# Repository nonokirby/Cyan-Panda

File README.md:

# Cyan Panda Expansion Gateway

The open-source hybrid can bus gateway !

Based heabily on the Racoon '[trash panda](https://github.com/mickabrig7/raccoon)'

more info coming **soon™**

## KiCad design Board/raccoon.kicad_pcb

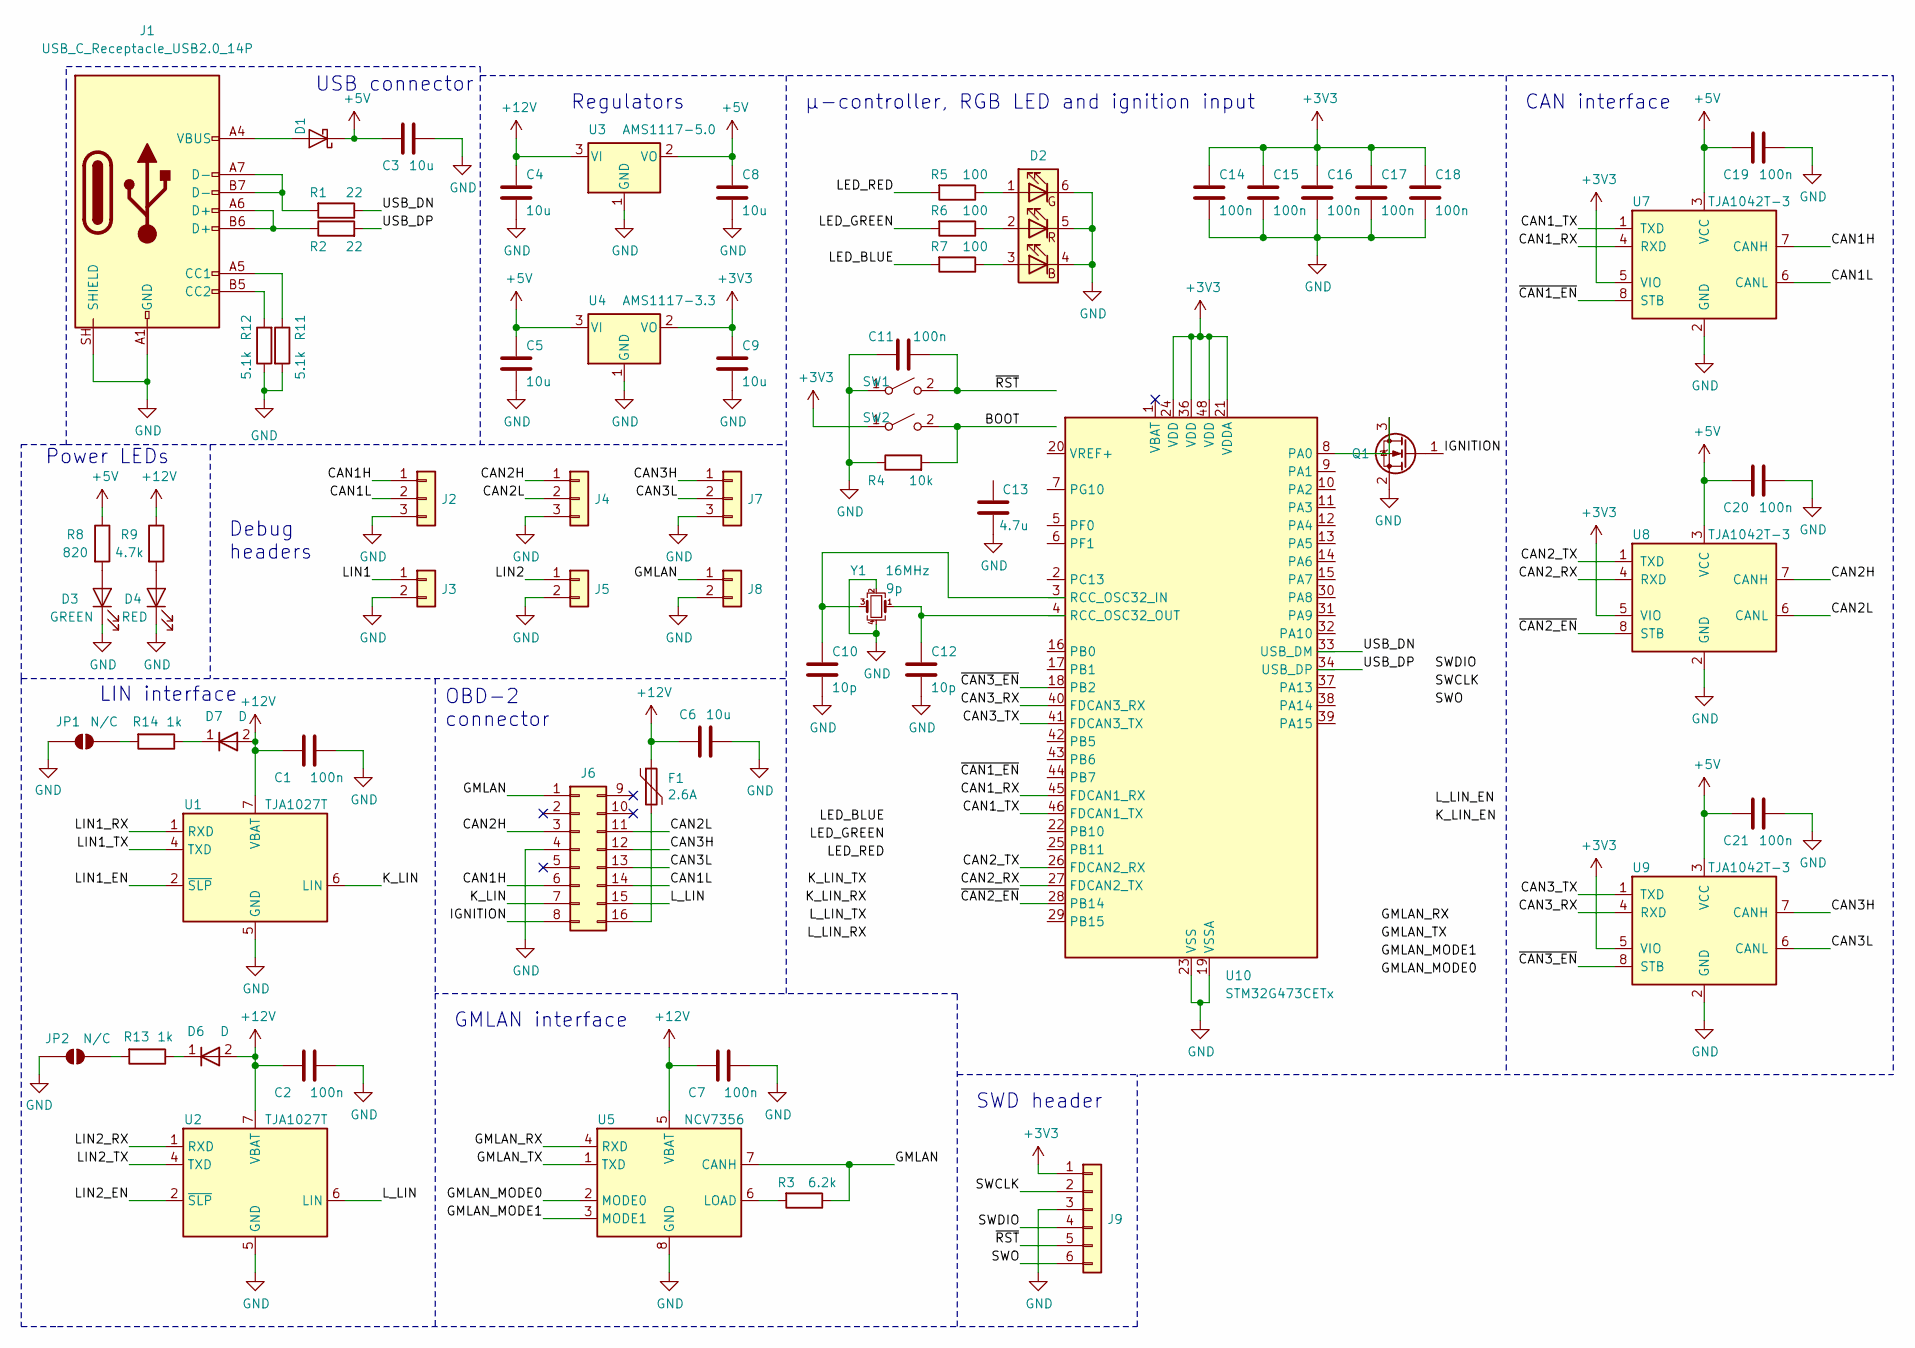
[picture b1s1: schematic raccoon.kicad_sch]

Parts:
C1, C2, C7, C11, C14, C15, C16, C17, C18, C19, C20, C21: 100n; C_0603_1608Metric; LCSC C14663
C3, C4, C5, C6, C8, C9: 10u; C_0805_2012Metric; LCSC C15850
C10, C12: 10p; C_0402_1005Metric; LCSC C32949
C13: 4.7u; C_0603_1608Metric; LCSC C19666
D1: D_Schottky; D_SMA; LCSC C8678
D2: LED_RGB; LED_RGB_5050-6
D3: GREEN; LED_0603_1608Metric_Castellated; LCSC C72043
D4: RED; LED_0603_1608Metric_Castellated; LCSC C2286
D6, D7: D; D_0603_1608Metric
F1: 2.6A; Fuse_1812_4532Metric
J1: USB_C_Receptacle_USB2.0_14P; USB_C_Receptacle_GCT_USB4105-xx-A_16P_TopMnt_Horizontal
J2, J4, J7: Conn_01x03; PinHeader_1x03_P2.54mm_Vertical
J3, J5, J8: Conn_01x02; PinHeader_1x02_P2.54mm_Vertical
J6: Conn_02x08_Top_Bottom; IDC-Header_2x08_P2.54mm_Vertical
J9: Conn_01x06; PinHeader_1x06_P2.54mm_Vertical
JP1, JP2: N/C; SolderJumper-2_P1.3mm_Open_RoundedPad1.0x1.5mm
Q1: Q_NMOS_GSD; SOT-23; LCSC C8545
R1, R2: 22; R_0603_1608Metric; LCSC C23345
R3: 6.2k; R_0603_1608Metric; LCSC C4260
R4: 10k; R_0603_1608Metric; LCSC C25804
R5, R6, R7: 100; R_0603_1608Metric; LCSC C22775
R8: 820; R_0603_1608Metric; LCSC C23253
R9: 4.7k; R_0603_1608Metric; LCSC C23162
R11, R12: 5.1k; R_01005_0402Metric
R13, R14: 1k; R_0402_1005Metric
SW1, SW2: SW_SPST; SW_PUSH_6mm_H8mm
U1, U2: TJA1027T; SOIC-8_3.9x4.9mm_P1.27mm
U3: AMS1117-5.0; SOT-223-3_TabPin2; LCSC C6187
U4: AMS1117-3.3; SOT-223-3_TabPin2; LCSC C6186
U5: NCV7356; SOIC-8_3.9x4.9mm_P1.27mm
U7, U8, U9: TJA1042T-3; SOIC-8_3.9x4.9mm_P1.27mm
U10: STM32G473CETx; LQFP-48_7x7mm_P0.5mm
Y1: 16MHz; Crystal_SMD_3225-4Pin_3.2x2.5mm; LCSC C13738

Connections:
+3V3: C9.1, C14.1, C15.1, C16.1, C17.1, C18.1, J9.1, SW2.1 (A), U4.2 (VO), U7.5 (VIO), U8.5 (VIO), U9.5 (VIO), U10.21 (VDDA), U10.24 (VDD), U10.36 (VDD), U10.48 (VDD)
+5V: C3.2, C5.1, C8.1, C19.2, C20.2, C21.2, D1.1 (K), R8.1, U3.2 (VO), U4.3 (VI), U7.3 (VCC), U8.3 (VCC), U9.3 (VCC)
+12V: C1.2, C2.2, C4.1, C6.2, C7.2, D6.2 (A), D7.2 (A), F1.1, R9.1, U1.7 (VBAT), U2.7 (VBAT), U3.3 (VI), U5.5 (VBAT)
/BOOT: R4.2, SW2.2 (B)
/CAN1H: J2.1, J6.6, U7.7 (CANH)
/CAN1L: J2.2, J6.14, U7.6 (CANL)
/CAN1_RX: U7.4 (RXD), U10.45 (FDCAN1_RX)
/CAN1_TX: U7.1 (TXD), U10.46 (FDCAN1_TX)
/CAN2H: J4.1, J6.3, U8.7 (CANH)
/CAN2L: J4.2, J6.11, U8.6 (CANL)
/CAN2_RX: U8.4 (RXD), U10.27 (FDCAN2_TX)
/CAN2_TX: U8.1 (TXD), U10.26 (FDCAN2_RX)
/CAN3H: J6.12, J7.1, U9.7 (CANH)
/CAN3L: J6.13, J7.2, U9.6 (CANL)
/CAN3_RX: U9.4 (RXD), U10.40 (FDCAN3_RX)
/CAN3_TX: U9.1 (TXD), U10.41 (FDCAN3_TX)
/GMLAN: J6.1, J8.1, R3.1, U5.7 (CANH)
/GMLAN_MODE0: U5.2 (MODE0)
/GMLAN_MODE1: U5.3 (MODE1)
/GMLAN_RX: U5.4 (RXD)
/GMLAN_TX: U5.1 (TXD)
/IGNITION: J6.8, Q1.1 (G)
/K_LIN: J6.7, U1.6 (LIN)
/LED_BLUE: R7.2
/LED_GREEN: R6.2
/LED_RED: R5.2
/LIN1: J3.1
/LIN1_EN: U1.2 (~SLP)
/LIN1_RX: U1.1 (RXD)
/LIN1_TX: U1.4 (TXD)
/LIN2: J5.1
/LIN2_EN: U2.2 (~SLP)
/LIN2_RX: U2.1 (RXD)
/LIN2_TX: U2.4 (TXD)
/L_LIN: J6.15, U2.6 (LIN)
/SWCLK: J9.2
/SWDIO: J9.4
/SWO: J9.6
/USB_DN: R1.1
/USB_DP: R2.2
/~CAN1_EN: U7.8 (STB), U10.16 (PB0)
/~CAN2_EN: U8.8 (STB), U10.28 (PB14)
/~CAN3_EN: U9.8 (STB), U10.18 (PB2)
/~RST: C11.1, J9.5, SW1.2 (B)
GND: C1.1, C2.1, C3.1, C4.2, C5.2, C6.1, C7.1, C8.2, C9.2, C10.2, C11.2, C12.2, C13.1, C14.2, C15.2, C16.2, C17.2, C18.2, C19.1, C20.1, C21.1, D2.4 (BK), D2.5 (GK), D2.6 (RK), D3.1 (K), D4.1 (K), J1.A1 (GND), J1.A12 (GND), J1.B1 (GND), J1.B12 (GND), J1.SH (SHIELD), J2.3, J3.2, J4.3, J5.2, J6.4, J7.3, J8.2, J9.3, JP1.1 (A), JP2.1 (A), Q1.2 (S), R4.1, R11.2, R12.1, SW1.1 (A), U1.5 (GND), U2.5 (GND), U3.1 (GND), U4.1 (GND), U5.8 (GND), U7.2 (GND), U8.2 (GND), U9.2 (GND), U10.19 (VSSA), U10.23 (VSS), U10.35 (VSS), U10.47 (VSS), Y1.2, Y1.4
unnamed: C10.1, Y1.3
unnamed: C12.1, Y1.1
unnamed: D1.2 (A), J1.A4 (VBUS), J1.A9 (VBUS), J1.B4 (VBUS), J1.B9 (VBUS)
unnamed: D2.3 (BA), R7.1
unnamed: D2.2 (GA), R6.1
unnamed: D2.1 (RA), R5.1
unnamed: D3.2 (A), R8.2
unnamed: D4.2 (A), R9.2
unnamed: D6.1 (K), R13.1
unnamed: D7.1 (K), R14.1
unnamed: J1.A5 (CC1), R11.1
unnamed: J1.B5 (CC2), R12.2
unnamed: J1.A6 (D+), J1.B6 (D+), R2.1
unnamed: J1.A7 (D-), J1.B7 (D-), R1.2
unnamed: F1.2, J6.16
unnamed: JP1.2 (B), R14.2
unnamed: JP2.2 (B), R13.2
unnamed: Q1.3 (D), U10.8 (PA0)
unnamed: R3.2, U5.6 (LOAD)

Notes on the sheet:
Power LEDs
GMLAN interface
USB connector
µ-controller, RGB LED and ignition input
LIN interface
OBD-2 connector
SWD header
CAN interface
Debug headers
Regulators

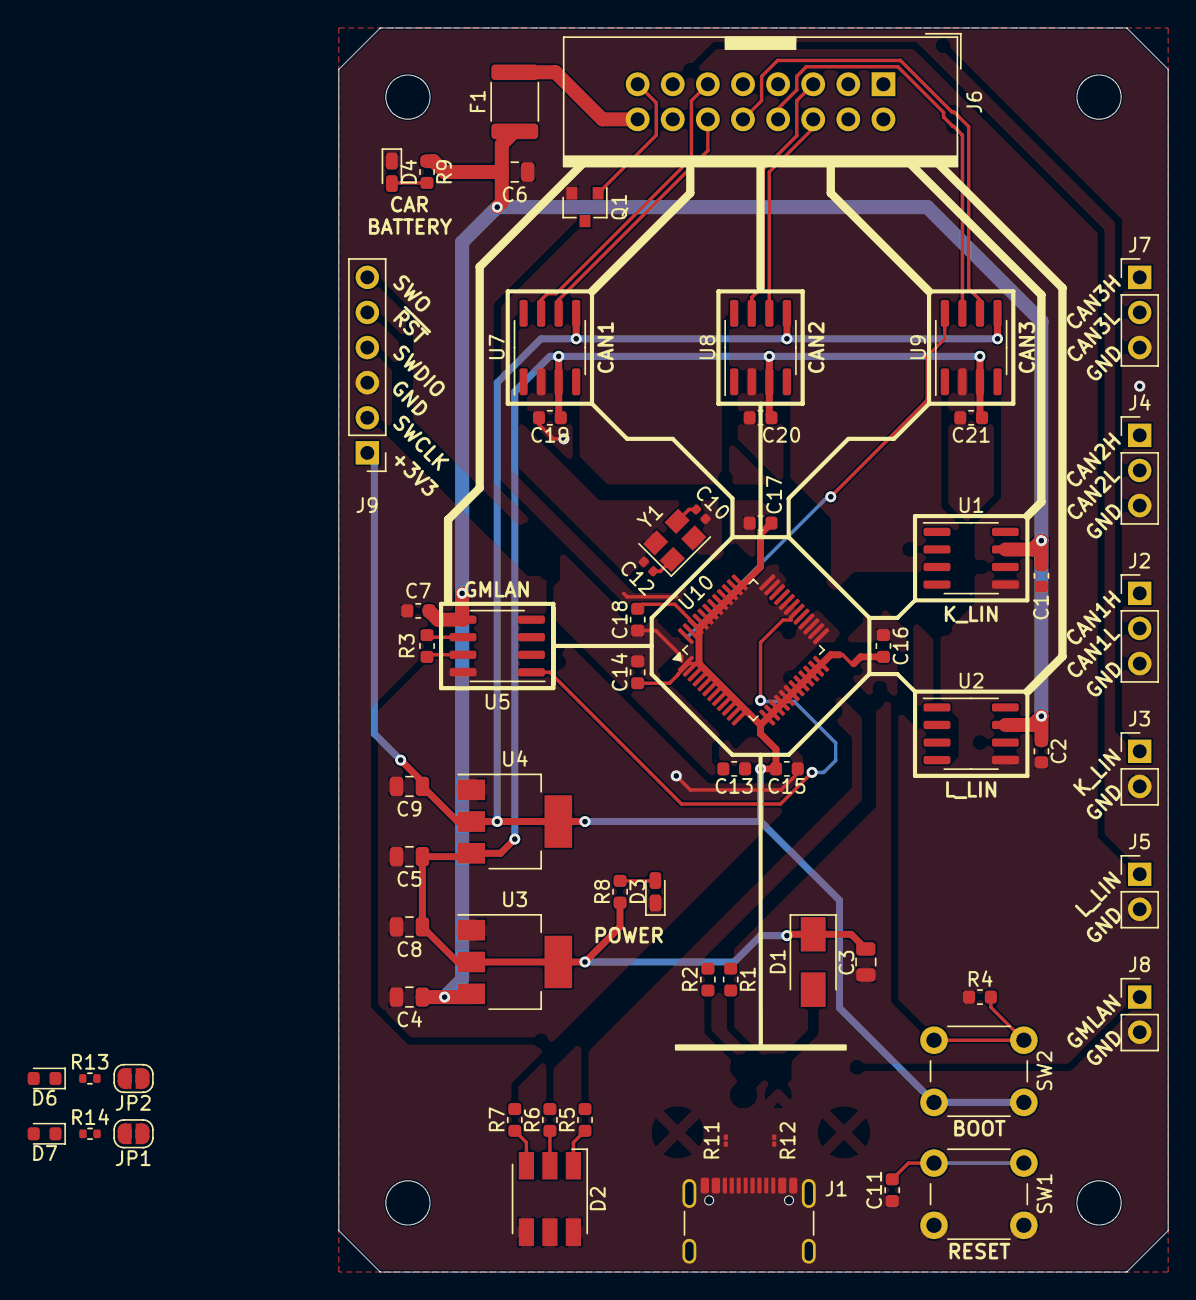
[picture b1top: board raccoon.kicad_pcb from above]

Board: 2 copper layers, 60.0 x 90.0 mm, 65 parts (0 on the bottom side), 44 nets.
